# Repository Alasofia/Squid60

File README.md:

# Squid60
GH60 Compatible PCB using Hi-Tek 725 Series (Space Invaders) switches.

Supports 8255C+/RT101 layouts.

Thanks to Engicoder and ai03 for the footprints and PCB design guide.

# Pictures

This work is licensed under the Creative Commons Attribution-NonCommercial 4.0 International License.

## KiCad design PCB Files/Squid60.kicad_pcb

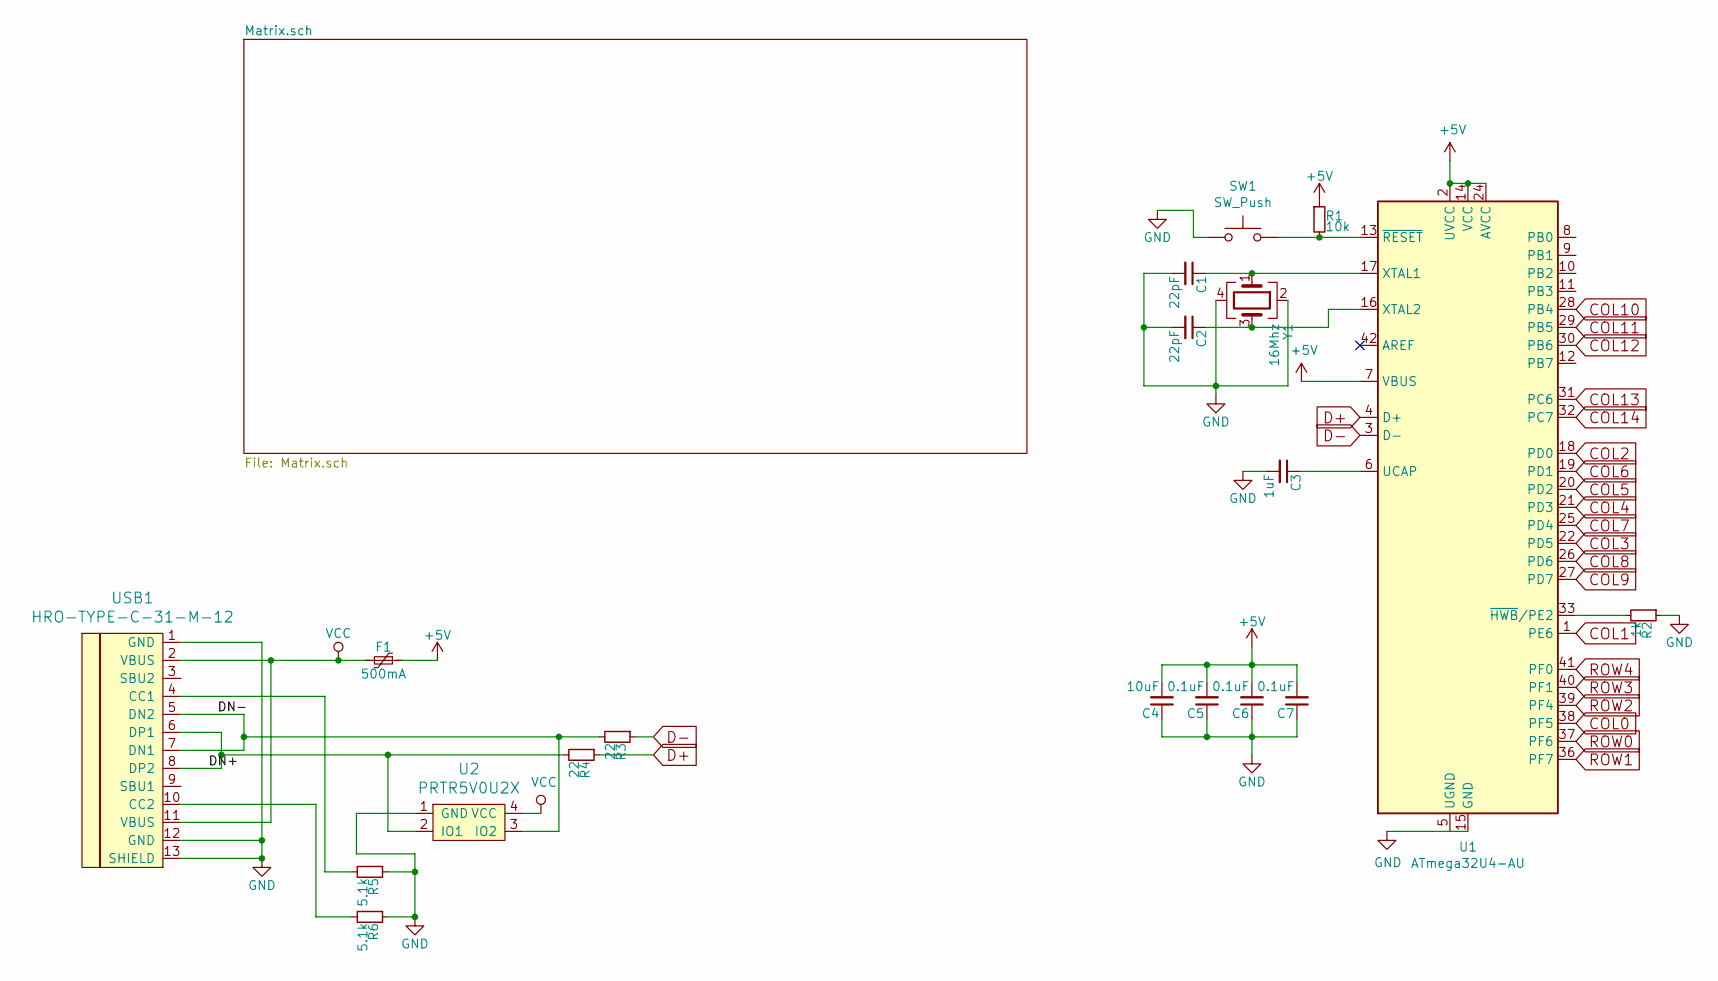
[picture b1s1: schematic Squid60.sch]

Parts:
C1, C2: 22pF; C_0805_2012Metric
C3: 1uF; C_0805_2012Metric
C4: 10uF; C_0805_2012Metric
C5, C6, C7: 0.1uF; C_0805_2012Metric
F1: 500mA; Fuse_1206_3216Metric
R1: 10k; R_0805_2012Metric
R2: 1k; R_0805_2012Metric
R3, R4: 22; R_0805_2012Metric
R5, R6: 5.1k; R_0805_2012Metric
SW1: SW_Push; PinSocket_1x02_P2.00mm_Horizontal
U1: ATmega32U4-AU; TQFP-44_10x10mm_P0.8mm
U2: PRTR5V0U2X; SOT143B
USB1: HRO-TYPE-C-31-M-12; HRO-TYPE-C-31-M-12-Assembly
Y1: 16Mhz; Crystal_SMD_3225-4Pin_3.2x2.5mm

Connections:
+5V: C4.2, C5.2, C6.2, C7.2, F1.1, R1.1, U1.2 (UVCC), U1.7 (VBUS), U1.14 (VCC), U1.24 (AVCC), U1.34 (VCC), U1.44 (AVCC)
/DN+: R4.2, U2.2 (IO1), USB1.6 (DP1), USB1.8 (DP2)
/DN-: R3.2, U2.3 (IO2), USB1.5 (DN2), USB1.7 (DN1)
COL0: U1.38 (PF5); also elsewhere on the board
COL1: U1.1 (PE6); also elsewhere on the board
COL2: U1.18 (PD0); also elsewhere on the board
COL3: U1.22 (PD5); also elsewhere on the board
COL4: U1.21 (PD3); also elsewhere on the board
COL5: U1.20 (PD2); also elsewhere on the board
COL6: U1.19 (PD1); also elsewhere on the board
COL7: U1.25 (PD4); also elsewhere on the board
COL8: U1.26 (PD6); also elsewhere on the board
COL9: U1.27 (PD7); also elsewhere on the board
COL10: U1.28 (PB4); also elsewhere on the board
COL11: U1.29 (PB5); also elsewhere on the board
COL12: U1.30 (PB6); also elsewhere on the board
COL13: U1.31 (PC6); also elsewhere on the board
COL14: U1.32 (PC7); also elsewhere on the board
D+: R4.1, U1.4 (D+)
D-: R3.1, U1.3 (D-)
GND: C1.2, C2.2, C3.2, C4.1, C5.1, C6.1, C7.1, R2.1, R5.1, R6.1, SW1.1, U1.15 (GND), U1.23 (GND), U1.35 (GND), U1.43 (GND), U2.1 (GND), USB1.1 (GND), USB1.12 (GND), USB1.13 (SHIELD), Y1.2, Y1.4
unnamed: C1.1, U1.17 (XTAL1), Y1.1
unnamed: C2.1, U1.16 (XTAL2), Y1.3
unnamed: C3.1, U1.6 (UCAP)
unnamed: R1.2, SW1.2, U1.13 (~RESET)
unnamed: R2.2, U1.33 (~HWB~/PE2)
unnamed: R5.2, USB1.4 (CC1)
unnamed: R6.2, USB1.10 (CC2)
ROW0: U1.37 (PF6); also elsewhere on the board
ROW1: U1.36 (PF7); also elsewhere on the board
ROW2: U1.39 (PF4); also elsewhere on the board
ROW3: U1.40 (PF1); also elsewhere on the board
ROW4: U1.41 (PF0); also elsewhere on the board
VCC: F1.2, U2.4 (VCC), USB1.2 (VBUS), USB1.11 (VBUS)

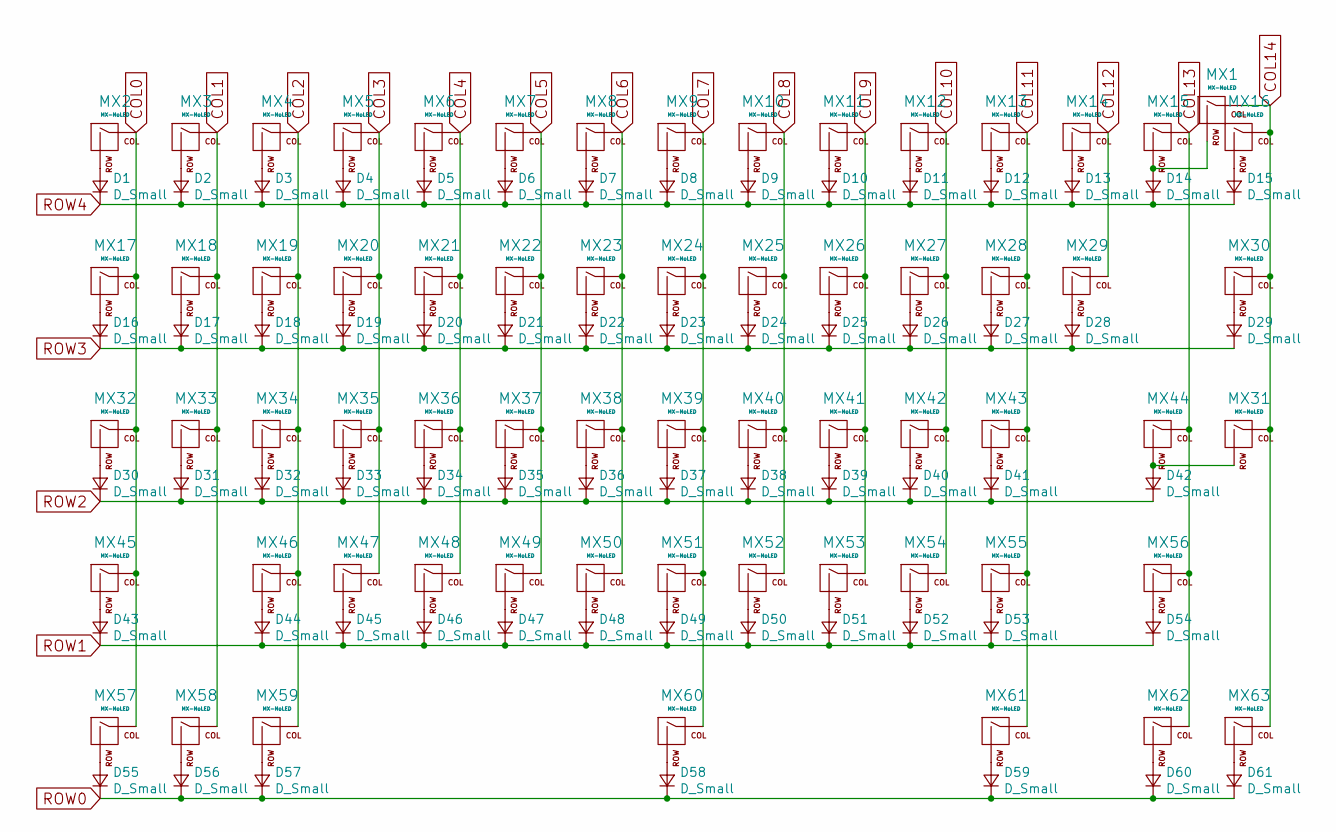
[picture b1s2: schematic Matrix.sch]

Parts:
D1, D2, D3, D4, D5, D6, D7, D8, D9, D10, D11, D12, D13, D14, D15, D16, D17, D18, D19, D20, D21, D22, D23, D24, D25, D26, D27, D28, D29, D30, D31, D32, D33, D34, D35, D36, D37, D38, D39, D40, D41, D42, D43, D44, D45, D46, D47, D48, D49, D50, D51, D52, D53, D54, D55, D56, D57, D58, D59, D60, D61: D_Small; D_SOD-123-Pretty
MX1: MX-NoLED; Hitek725-2U
MX2, MX3, MX4, MX5, MX6, MX7, MX8, MX9, MX10, MX11, MX12, MX13, MX14, MX15, MX16, MX18, MX19, MX20, MX21, MX22, MX23, MX24, MX25, MX26, MX27, MX28, MX29, MX33, MX34, MX35, MX36, MX37, MX38, MX39, MX40, MX41, MX42, MX43, MX46, MX47, MX48, MX49, MX50, MX51, MX52, MX53, MX54, MX55, MX58, MX62: MX-NoLED; Hitek725-1U
MX17, MX30, MX57, MX59, MX61, MX63: MX-NoLED; Hitek725-1.5U
MX31: MX-NoLED; Hitek725-BigAssEnter
MX32: MX-NoLED; Hitek725-1.75U
MX44, MX45: MX-NoLED; Hitek725-2.25U
MX56: MX-NoLED; Hitek725-2.75U
MX60: MX-NoLED; Hitek725-7U

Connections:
COL0: MX2.1 (COL), MX17.1 (COL), MX32.1 (COL), MX45.1 (COL), MX57.1 (COL); also elsewhere on the board
COL1: MX3.1 (COL), MX18.1 (COL), MX33.1 (COL), MX58.1 (COL); also elsewhere on the board
COL2: MX4.1 (COL), MX19.1 (COL), MX34.1 (COL), MX46.1 (COL), MX59.1 (COL); also elsewhere on the board
COL3: MX5.1 (COL), MX20.1 (COL), MX35.1 (COL), MX47.1 (COL); also elsewhere on the board
COL4: MX6.1 (COL), MX21.1 (COL), MX36.1 (COL), MX48.1 (COL); also elsewhere on the board
COL5: MX7.1 (COL), MX22.1 (COL), MX37.1 (COL), MX49.1 (COL); also elsewhere on the board
COL6: MX8.1 (COL), MX23.1 (COL), MX38.1 (COL), MX50.1 (COL); also elsewhere on the board
COL7: MX9.1 (COL), MX24.1 (COL), MX39.1 (COL), MX51.1 (COL), MX60.1 (COL); also elsewhere on the board
COL8: MX10.1 (COL), MX25.1 (COL), MX40.1 (COL), MX52.1 (COL); also elsewhere on the board
COL9: MX11.1 (COL), MX26.1 (COL), MX41.1 (COL), MX53.1 (COL); also elsewhere on the board
COL10: MX12.1 (COL), MX27.1 (COL), MX42.1 (COL), MX54.1 (COL); also elsewhere on the board
COL11: MX13.1 (COL), MX28.1 (COL), MX43.1 (COL), MX55.1 (COL), MX61.1 (COL); also elsewhere on the board
COL12: MX14.1 (COL), MX29.1 (COL); also elsewhere on the board
COL13: MX15.1 (COL), MX44.1 (COL), MX56.1 (COL), MX62.1 (COL); also elsewhere on the board
COL14: MX1.1 (COL), MX16.1 (COL), MX30.1 (COL), MX31.1 (COL), MX63.1 (COL); also elsewhere on the board
unnamed: D1.2 (A), MX2.2 (ROW)
unnamed: D2.2 (A), MX3.2 (ROW)
unnamed: D3.2 (A), MX4.2 (ROW)
unnamed: D4.2 (A), MX5.2 (ROW)
unnamed: D5.2 (A), MX6.2 (ROW)
unnamed: D6.2 (A), MX7.2 (ROW)
unnamed: D7.2 (A), MX8.2 (ROW)
unnamed: D8.2 (A), MX9.2 (ROW)
unnamed: D9.2 (A), MX10.2 (ROW)
unnamed: D10.2 (A), MX11.2 (ROW)
unnamed: D11.2 (A), MX12.2 (ROW)
unnamed: D12.2 (A), MX13.2 (ROW)
unnamed: D13.2 (A), MX14.2 (ROW)
unnamed: D14.2 (A), MX1.2 (ROW), MX15.2 (ROW)
unnamed: D15.2 (A), MX16.2 (ROW)
unnamed: D16.2 (A), MX17.2 (ROW)
unnamed: D17.2 (A), MX18.2 (ROW)
unnamed: D18.2 (A), MX19.2 (ROW)
unnamed: D19.2 (A), MX20.2 (ROW)
unnamed: D20.2 (A), MX21.2 (ROW)
unnamed: D21.2 (A), MX22.2 (ROW)
unnamed: D22.2 (A), MX23.2 (ROW)
unnamed: D23.2 (A), MX24.2 (ROW)
unnamed: D24.2 (A), MX25.2 (ROW)
unnamed: D25.2 (A), MX26.2 (ROW)
unnamed: D26.2 (A), MX27.2 (ROW)
unnamed: D27.2 (A), MX28.2 (ROW)
unnamed: D28.2 (A), MX29.2 (ROW)
unnamed: D29.2 (A), MX30.2 (ROW)
unnamed: D30.2 (A), MX32.2 (ROW)
unnamed: D31.2 (A), MX33.2 (ROW)
unnamed: D32.2 (A), MX34.2 (ROW)
unnamed: D33.2 (A), MX35.2 (ROW)
unnamed: D34.2 (A), MX36.2 (ROW)
unnamed: D35.2 (A), MX37.2 (ROW)
unnamed: D36.2 (A), MX38.2 (ROW)
unnamed: D37.2 (A), MX39.2 (ROW)
unnamed: D38.2 (A), MX40.2 (ROW)
unnamed: D39.2 (A), MX41.2 (ROW)
unnamed: D40.2 (A), MX42.2 (ROW)
unnamed: D41.2 (A), MX43.2 (ROW)
unnamed: D42.2 (A), MX31.2 (ROW), MX44.2 (ROW)
unnamed: D43.2 (A), MX45.2 (ROW)
unnamed: D44.2 (A), MX46.2 (ROW)
unnamed: D45.2 (A), MX47.2 (ROW)
unnamed: D46.2 (A), MX48.2 (ROW)
unnamed: D47.2 (A), MX49.2 (ROW)
unnamed: D48.2 (A), MX50.2 (ROW)
unnamed: D49.2 (A), MX51.2 (ROW)
unnamed: D50.2 (A), MX52.2 (ROW)
unnamed: D51.2 (A), MX53.2 (ROW)
unnamed: D52.2 (A), MX54.2 (ROW)
unnamed: D53.2 (A), MX55.2 (ROW)
unnamed: D54.2 (A), MX56.2 (ROW)
unnamed: D55.2 (A), MX57.2 (ROW)
unnamed: D56.2 (A), MX58.2 (ROW)
unnamed: D57.2 (A), MX59.2 (ROW)
unnamed: D58.2 (A), MX60.2 (ROW)
unnamed: D59.2 (A), MX61.2 (ROW)
unnamed: D60.2 (A), MX62.2 (ROW)
unnamed: D61.2 (A), MX63.2 (ROW)
ROW0: D55.1 (K), D56.1 (K), D57.1 (K), D58.1 (K), D59.1 (K), D60.1 (K), D61.1 (K); also elsewhere on the board
ROW1: D43.1 (K), D44.1 (K), D45.1 (K), D46.1 (K), D47.1 (K), D48.1 (K), D49.1 (K), D50.1 (K), D51.1 (K), D52.1 (K), D53.1 (K), D54.1 (K); also elsewhere on the board
ROW2: D30.1 (K), D31.1 (K), D32.1 (K), D33.1 (K), D34.1 (K), D35.1 (K), D36.1 (K), D37.1 (K), D38.1 (K), D39.1 (K), D40.1 (K), D41.1 (K), D42.1 (K); also elsewhere on the board
ROW3: D16.1 (K), D17.1 (K), D18.1 (K), D19.1 (K), D20.1 (K), D21.1 (K), D22.1 (K), D23.1 (K), D24.1 (K), D25.1 (K), D26.1 (K), D27.1 (K), D28.1 (K), D29.1 (K); also elsewhere on the board
ROW4: D1.1 (K), D2.1 (K), D3.1 (K), D4.1 (K), D5.1 (K), D6.1 (K), D7.1 (K), D8.1 (K), D9.1 (K), D10.1 (K), D11.1 (K), D12.1 (K), D13.1 (K), D14.1 (K), D15.1 (K); also elsewhere on the board

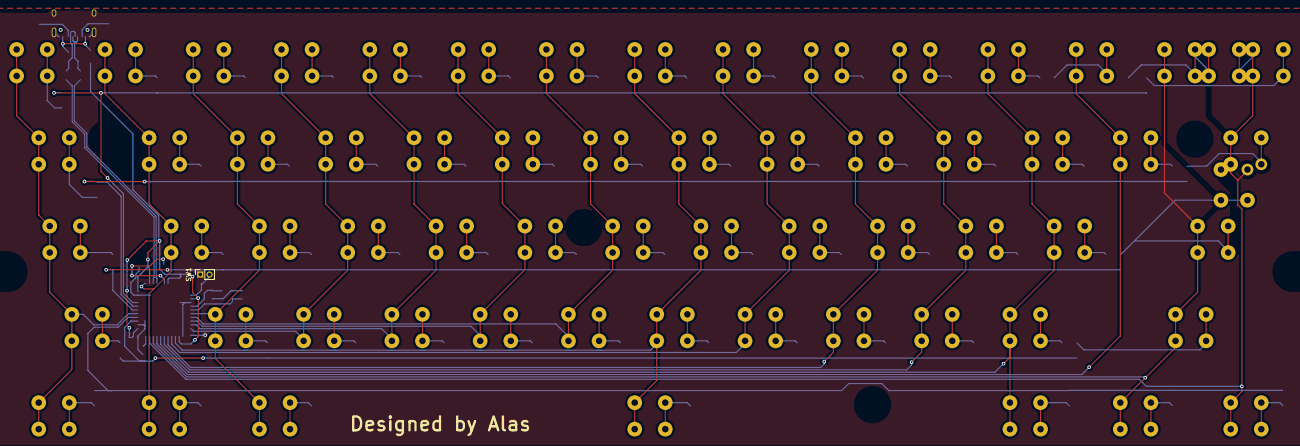
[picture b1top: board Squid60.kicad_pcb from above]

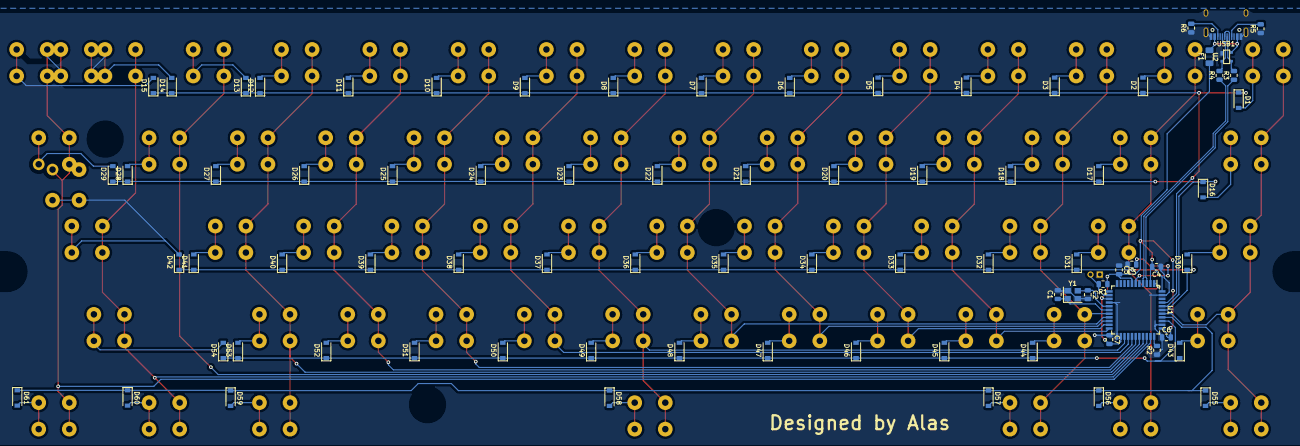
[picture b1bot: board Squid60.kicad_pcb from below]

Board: 2 copper layers, 143 parts (81 on the bottom side), 95 nets.

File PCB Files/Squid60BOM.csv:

"Id";"Designator";"Package";"Quantity";"Designation";"Supplier and ref";
1;"REF**";"60_Outline-Modded";1;"60_Outline";;;
2;"SW1";"PinSocket_1x02_P2.00mm_Vertical";1;"SW_Push";;;
3;"Y1";"Crystal_SMD_3225-4Pin_3.2x2.5mm";1;"16Mhz";;;
4;"F1";"Fuse_1206_3216Metric";1;"500mA";;;
5;"C7,C6,C5";"C_0805_2012Metric";3;"0.1uF";;;
6;"C4";"C_0805_2012Metric";1;"10uF";;;
7;"C3";"C_0805_2012Metric";1;"1uF";;;
8;"C2,C1";"C_0805_2012Metric";2;"22pF";;;
9;"R6,R5";"R_0805_2012Metric";2;"5.1k";;;
10;"R4,R3";"R_0805_2012Metric";2;"22";;;
11;"R2";"R_0805_2012Metric";1;"1k";;;
12;"R1";"R_0805_2012Metric";1;"10k";;;
13;"U1";"TQFP-44_10x10mm_P0.8mm";1;"ATmega32U4-AU";;;
14;"MX44,MX45";"Hitek725-2.25U";2;"MX-NoLED";;;
15;"MX63,MX61,MX59,MX57,MX30,MX17";"Hitek725-1.5U";6;"MX-NoLED";;;
16;"MX62,MX58,MX55,MX54,MX53,MX52,MX51,MX50,MX49,MX48,MX47,MX46,MX43,MX42,MX41,MX40,MX39,MX38,MX37,MX36,MX35,MX34,MX33,MX29,MX28,MX27,MX26,MX25,MX24,MX23,MX22,MX21,MX20,MX19,MX18,MX16,MX15,MX14,MX13,MX12,MX11,MX10,MX9,MX8,MX7,MX6,MX5,MX4,MX3,MX2";"Hitek725-1U";50;"MX-NoLED";;;
17;"USB1";"HRO-TYPE-C-31-M-12-Assembly";1;"HRO-TYPE-C-31-M-12";;;
18;"U2";"SOT143B";1;"PRTR5V0U2X";;;
19;"MX31";"Hitek725-BigAssEnter";1;"MX-NoLED";;;
20;"MX1";"Hitek725-2U";1;"MX-NoLED";;;
21;"MX60";"Hitek725-7U";1;"MX-NoLED";;;
22;"MX56";"Hitek725-2.75U";1;"MX-NoLED";;;
23;"MX32";"Hitek725-1.75U";1;"MX-NoLED";;;
24;"D61,D60,D59,D58,D57,D56,D55,D54,D53,D52,D51,D50,D49,D48,D47,D46,D45,D44,D43,D42,D41,D40,D39,D38,D37,D36,D35,D34,D33,D32,D31,D30,D29,D28,D27,D26,D25,D24,D23,D22,D21,D20,D19,D18,D17,D16,D15,D14,D13,D12,D11,D10,D9,D8,D7,D6,D5,D4,D3,D2,D1";"D_SOD-123-Pretty";61;"D_Small";;;

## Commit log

2020-04-19 Organization and images
2020-04-19 Silkscreens
2020-04-19 Couple Fixes
    row 3 wasn't routed, row 1 had not been finished
2020-04-19 Redid Gerbers to reflect last commit
2020-04-19 Removed Silkscreens
    Because I don't to get sued
    Also redid gerbers for that because again, yikes
2020-04-20 Updated images in readme
    and updated gerbers to be sure they're correct
2020-04-20 Ignore previous commit
    I'm dumb, THIS commit fixes those things
2020-04-25 added fr4 plate files
2020-07-15 Fixed up the overlapping footprints and zipped gerbers
2021-11-24 Add License
